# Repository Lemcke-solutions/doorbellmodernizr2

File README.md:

This repository contains sample code and eagle/gerber/STL files for the Doorbell Modernizr 2 that is for sale on tindie: https://www.tindie.com/products/ErikLemcke/doorbell-modernizr-2/

The Doorbell Modernizr is a device that can transform your ordinary doorbell (running on 8 - 24v ac) into a "smart" wifi doorbell.
Whenever someone presses your doorbell, the Doorbell Modernizr can send a signal to your home automation system (currently supported: Home assistant, Domoticz and Openhab).
With the doorbell modernizr 2 it is also possible to turn your doorbell on and off from your home automation system.

If you want to program the device yourself (for example with the Arduino IDE), you can do so by connecting it via USB to your computer.

I use the folowing settings for programming:

- Board: Generic EP8266 module
- Flash mode: QIO
- Flash size: 512K (64K SPIFFS)
- Debugging port: Disabled
- Debug level: None
- IwIP variant: V2 lower memory
- reset method: ck
- crystal frequency: 26Mhz
- Flash frequency: 40Mhz
- CPU frequency: 80Mhz
- Builtin led: 2
- Upload speed: 115200
- Erase flash: Only sketch

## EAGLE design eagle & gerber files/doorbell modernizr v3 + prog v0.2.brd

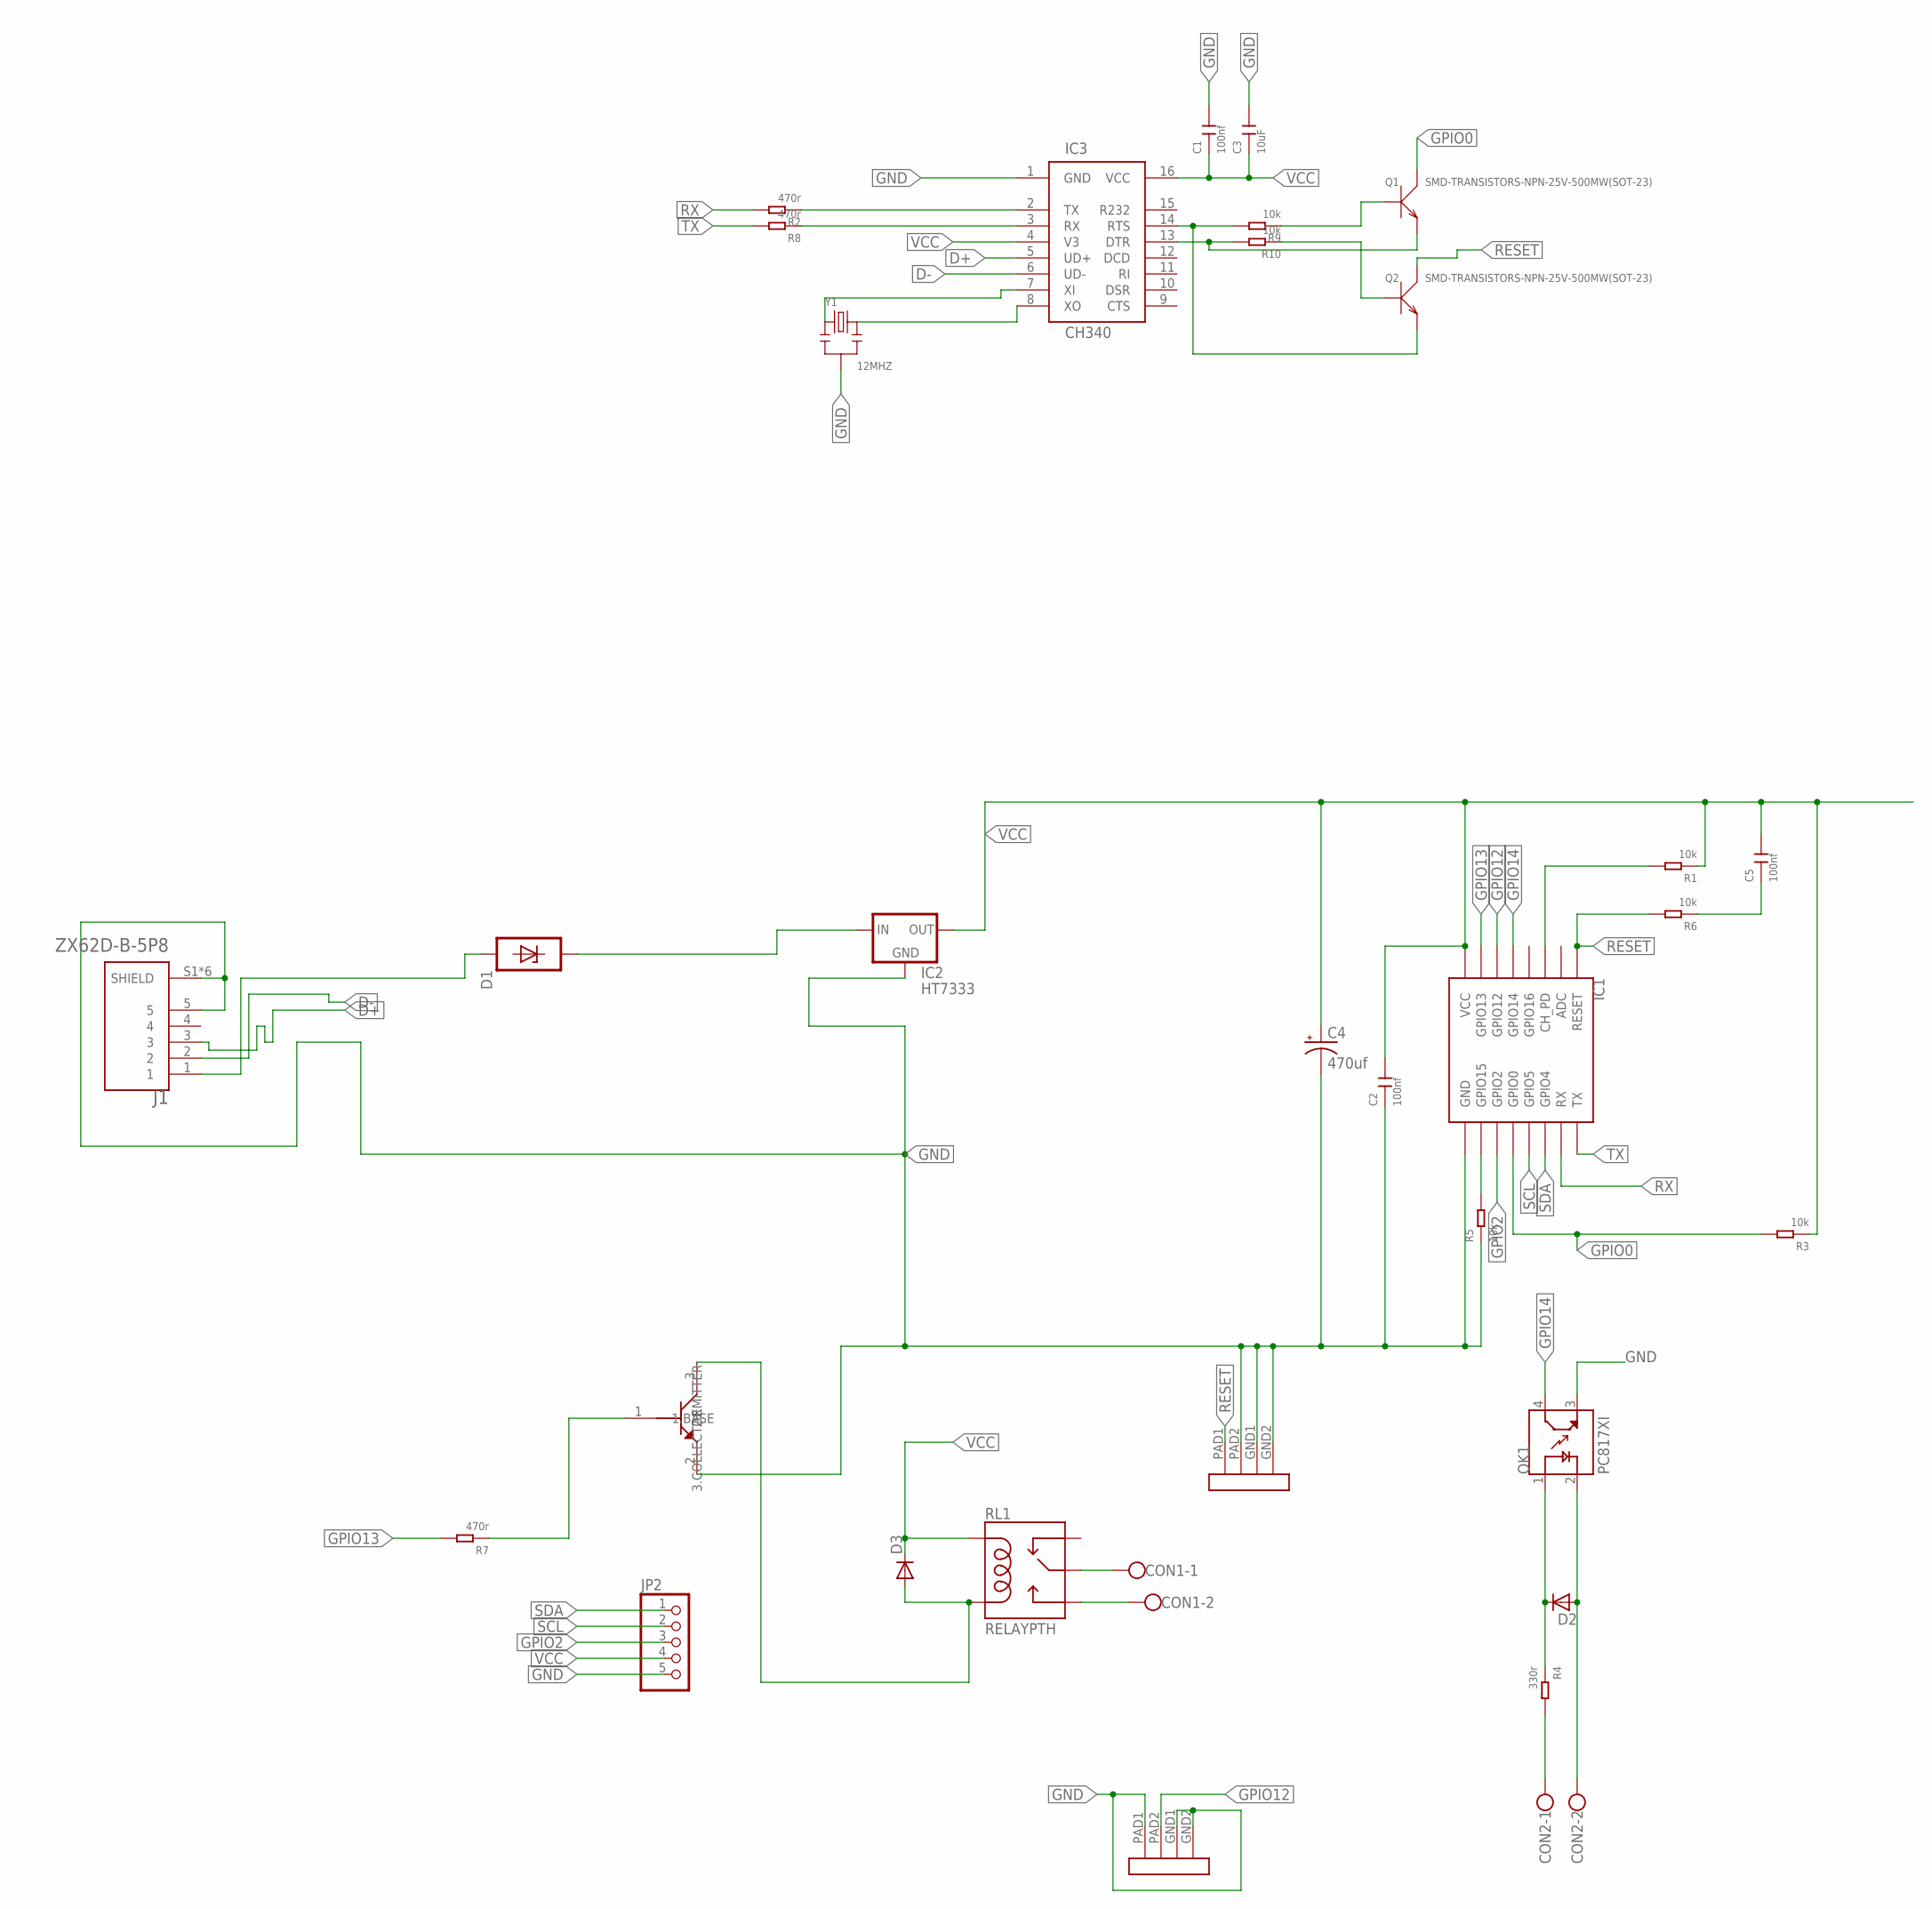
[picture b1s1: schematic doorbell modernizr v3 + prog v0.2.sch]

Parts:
C1, C2, C5: 100nf; C0603
C3: 10uF; C0603
C4: 470uf; PANASONIC_D
CON1, CON2: W237-102
D1: SP4020-01FTG; SOD323
D2: D-SOD123; SOD123
D3: DIODE-SOD123; SOD123
IC1: ESP12SMD; ESP12-SMD
IC2: HT7333; SOT-89
IC3: CH340; SOIC16
J1: ZX62D-B-5P8; HRS_ZX62D-B-5P8
JP2: PINHD-1X5; 1X05
OK1: PC817XI; SOIC254P975X460-4N
Q1, Q2: SMD-TRANSISTORS-NPN-25V-500MW(SOT-23); SOT-23
Q3: 2N2222; SOT23
R1, R3, R5, R6, R9, R10: 10k; R0603
R2, R7, R8: 470r; R0603
R4: 330r; R0603
RL1: RELAYPTH; SRD-05VDC-SL-C
SW1, SW2: MINI-SIDE-SWITCH
Y1: 12MHZ; X3-SMD-3.6X1.3X0.8MM

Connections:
D+: IC3.5 (UD+), J1.3
D-: IC3.6 (UD-), J1.2
GND: C1.2, C2.1, C3.2, C4.-, IC1.GND, IC2.2 (GND), IC3.1 (GND), J1.5, J1.S1 (SHIELD), J1.S2 (SHIELD), J1.S3 (SHIELD), J1.S4 (SHIELD), J1.S5 (SHIELD), J1.S6 (SHIELD), JP2.5, OK1.3 (ET), Q3.2 (2.EMITTER), R5.1, SW1.GND1, SW1.GND2, SW1.PAD2, SW2.GND1, SW2.GND2, SW2.PAD1, Y1.2
GPIO0: IC1.GPIO0, Q1.3 (C), R3.2
GPIO2: IC1.GPIO2, JP2.3
GPIO12: IC1.GPIO12, SW2.PAD2
GPIO13: IC1.GPIO13, R7.2
GPIO14: IC1.GPIO14, OK1.4 (CT)
unnamed: IC1.GPIO15, R5.2
unnamed: D3.A, Q3.3 (3.COLLECTOR), RL1.COIL0
unnamed: D2.1 (C), OK1.1 (A), R4.1
unnamed: CON2.2, D2.2 (A), OK1.2 (C)
unnamed: IC1.CH_PD, R1.2
unnamed: CON2.1, R4.2
unnamed: CON1.2, RL1.SWOPEN
unnamed: IC3.2 (TX), R2.1
unnamed: D1.1, IC2.4 (IN), IC2.P$2 (IN)
unnamed: CON1.1, RL1.SWCOMMON
unnamed: IC3.3 (RX), R8.1
unnamed: Q3.1 (1.BASE), R7.1
unnamed: IC3.14 (RTS), Q2.2 (E), R9.2
unnamed: IC3.13 (DTR), Q1.2 (E), R10.2
unnamed: Q1.1 (B), R9.1
unnamed: Q2.1 (B), R10.1
unnamed: IC3.8 (XO), Y1.3
unnamed: IC3.7 (XI), Y1.1
unnamed: D1.2, J1.1
unnamed: C5.1, R6.1
RESET: IC1.RESET, Q2.3 (C), R6.2, SW1.PAD1
RX: IC1.RXD0 (RX), R2.2
SCL: IC1.GPIO5, JP2.2
SDA: IC1.GPIO4, JP2.1
TX: IC1.TXD0 (TX), R8.2
VCC: C1.1, C2.2, C3.1, C4.+, C5.2, D3.C, IC1.VCC, IC2.1 (OUT), IC3.4 (V3), IC3.16 (VCC), JP2.4, R1.1, R3.1, RL1.COIL1

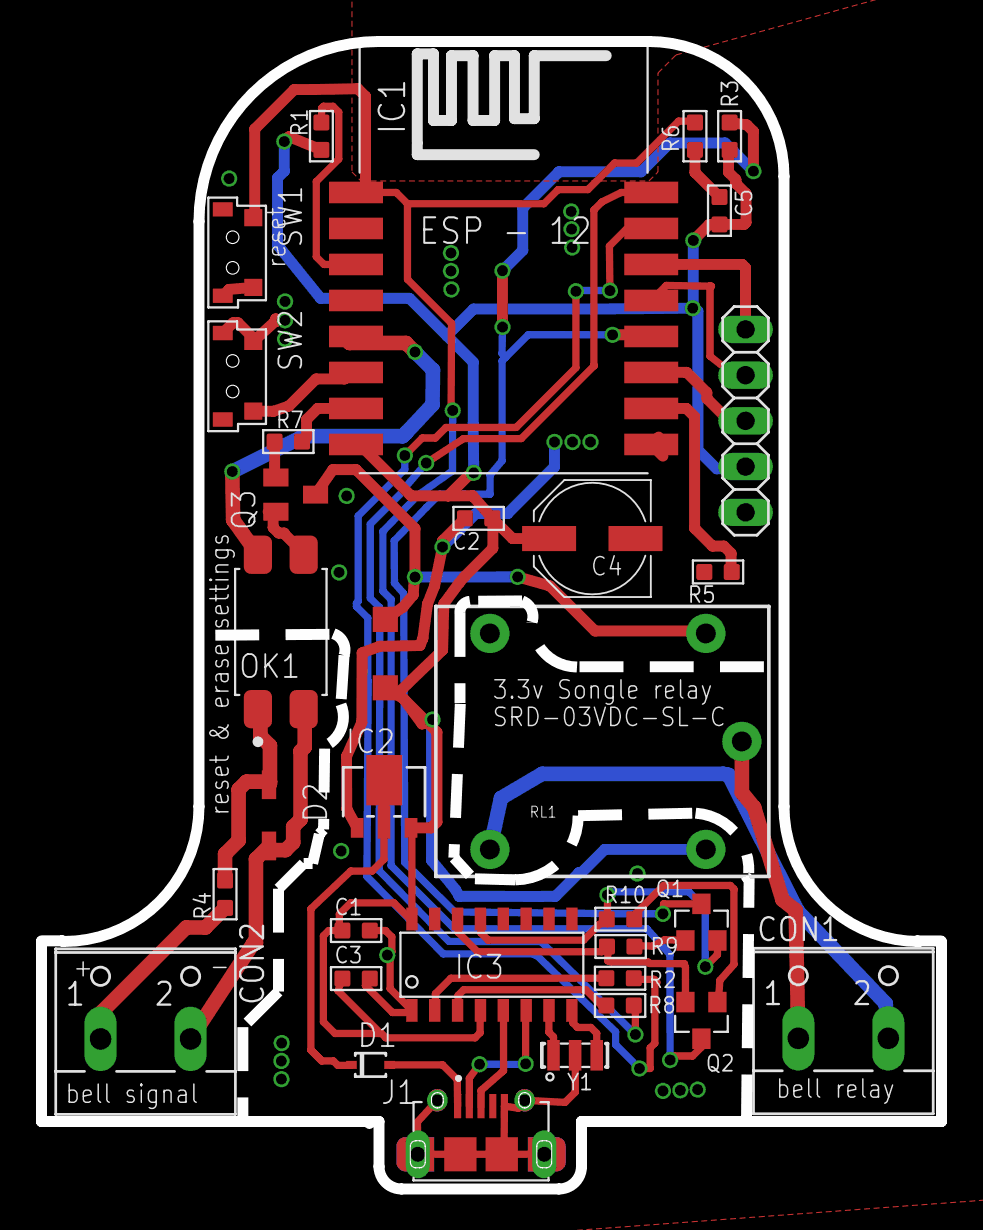
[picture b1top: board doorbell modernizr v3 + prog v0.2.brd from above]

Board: 2 copper layers, 50.0 x 63.8 mm, 33 parts (0 on the bottom side), 34 nets.

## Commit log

2020-08-16 arduino files
2020-08-16 manual & 3d files
2020-08-17 eagle and gerber files
2020-08-31 text fixes
2020-08-31 disable debug
2020-08-31 text changes

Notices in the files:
parts and their libraries:
SparkFun-Capacitors: Licensing: Creative Commons ShareAlike 4.0 International - https://creativecommons.org/licenses/by-sa/4.0
